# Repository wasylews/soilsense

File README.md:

# SoilSense

A low-power soil moisture and climate sensor for your garden. It samples capacitive soil moisture, temperature, and humidity, then reports them to Home Assistant. The whole device runs on an ESP-01 and is powered by a single 18650 cell, good for roughly six months per charge. It lives in a 3D-printed enclosure you can print at home.

## Features

- Battery-operated ESP-01 that deep-sleeps between readings to stretch battery life
- Single 18650 cell, estimated six months per charge
- Capacitive soil moisture probe sampled through an ADS1115 ADC
- GXHT30 digital temperature and humidity sensor
- Publishes over MQTT and the Home Assistant API, with OTA updates
- Custom two-layer PCB with a TP4056 lithium battery charger
- 3D-printed case and lid, modeled in FreeCAD and exported as STL

## Design notes

Why an ESP-01? At the time it was the smallest board I had on hand, and that was the point. I wanted to see how little hardware could still run a useful garden sensor. An ESP32 would have made this easier; it even has ADCs onboard, but easier was not the goal.

The ESP-01 has no ADC on the module, so the probe reads through an external ADS1115 on the same I2C bus as the GXHT30. The 16-bit ADC is overkill for a moisture probe, but it keeps the analog side out of the firmware and the whole board on two wires.

Deep sleep is what makes the battery life work. Between readings the chip sleeps, so the sensor sits in the soil without a cable and without frequent recharges.

## Design

### Electronics

The schematic and PCB are designed in KiCad and live in `design/soilsense/`. The board hosts an ESP-01 module, the TP4056 charger, and an I2C bus that connects the ADS1115 and the GXHT30. While the design was being refined, several board variants were explored (30x70 mm, 50x70 mm, and one rotated ESP layout); the main board is `soilsense.kicad_pcb`.

### Firmware

The firmware is an ESPHome config, `firmware/soilsense.yaml`. It reads the sensors over I2C, publishes to Home Assistant, and puts the chip to deep sleep. WiFi credentials and API keys live in a gitignored `secrets.yaml`. Flash it with:

```
esphome run soilsense.yaml
```

### Enclosure

The case is modeled in FreeCAD (`design/enclosure.FCStd`) and exported as STL for printing (`design/enclosure-case.stl` and `design/enclosure-lid.stl`). The lid snaps over the case, and the base carries a slot for the moisture probe.

## Repository layout

```
design/
  enclosure.FCStd                  FreeCAD source of the case
  enclosure-case.stl               case, ready to print
  enclosure-lid.stl                lid, ready to print
  soilsense/                       KiCad project (schematic, PCB, board variants)
firmware/
  soilsense.yaml                   ESPHome configuration
images/
  board render, PCB layout, schematic and enclosure photos
```

## Images

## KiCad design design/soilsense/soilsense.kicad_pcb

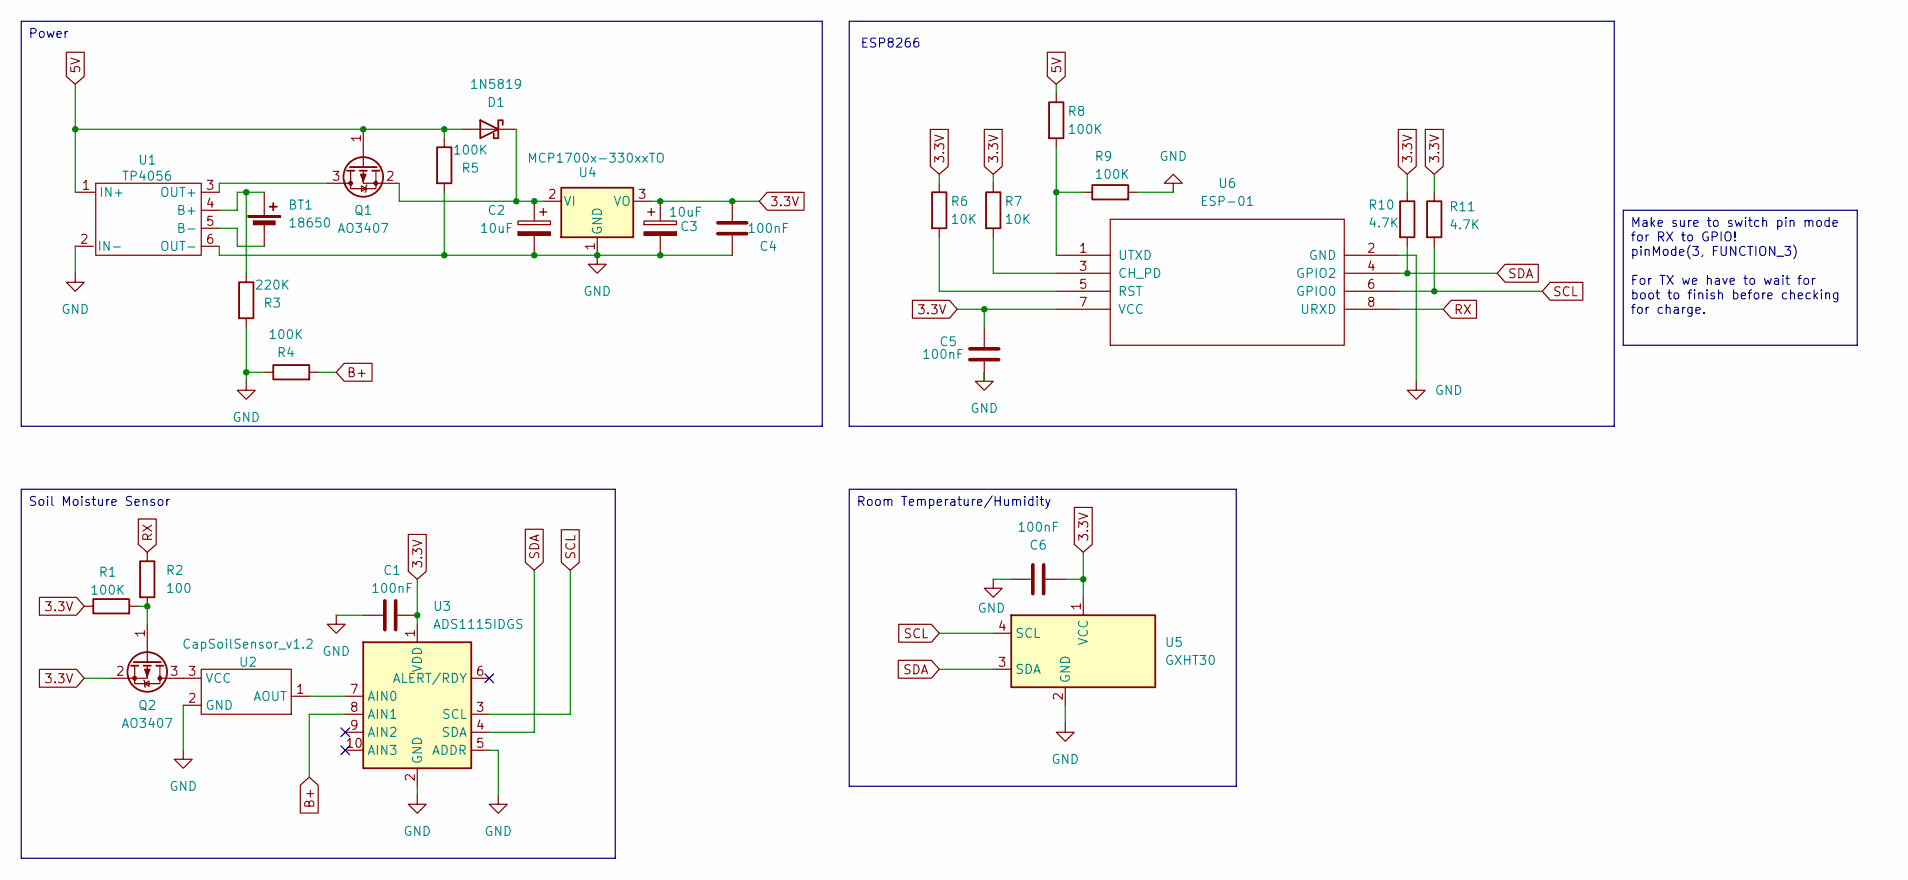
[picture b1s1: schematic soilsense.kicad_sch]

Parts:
BT1: 18650
C1, C4, C5, C6: 100nF; C_Disc_D5.0mm_W2.5mm_P5.00mm
C2, C3: 10uF; CP_Radial_D5.0mm_P2.00mm
D1: 1N5819; D_DO-41_SOD81_P10.16mm_Horizontal
Q1, Q2: AO3407; PinHeader_1x03_P2.54mm_Vertical
R1, R4, R5, R8, R9: 100K; R_Axial_DIN0204_L3.6mm_D1.6mm_P5.08mm_Horizontal
R2: 100; R_Axial_DIN0204_L3.6mm_D1.6mm_P5.08mm_Horizontal
R3: 220K; R_Axial_DIN0204_L3.6mm_D1.6mm_P5.08mm_Horizontal
R6, R7: 10K; R_Axial_DIN0204_L3.6mm_D1.6mm_P5.08mm_Horizontal
R10, R11: 4.7K; R_Axial_DIN0204_L3.6mm_D1.6mm_P5.08mm_Horizontal
U1: TP4056
U2: CapSoilSensor_v1.2; PinHeader_1x03_P2.54mm_Vertical
U3: ADS1115IDGS; PinHeader_1x10_P2.54mm_Vertical
U4: MCP1700x-330xxTO; TO-92
U5: GXHT30; PinSocket_1x04_P2.54mm_Vertical
U6: ESP-01

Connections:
3.3V: C1.2, C3.1, C4.1, C5.2, C6.2, Q2.2 (S), R1.1, R6.1, R7.1, R10.1, R11.1, U3.1 (VDD), U4.3 (VO), U5.1 (VCC), U6.7 (VCC)
5V: D1.2 (A), Q1.1 (G), R5.1, R8.1, U1.1 (IN+)
B+: R4.2, U3.8 (AIN1)
GND: C1.1, C2.2, C3.2, C4.2, C5.1, C6.1, R3.2, R4.1, R5.2, R9.2, U1.2 (IN-), U1.6 (OUT-), U2.2 (GND), U3.2 (GND), U3.5 (ADDR), U4.1 (GND), U5.2 (GND), U6.2 (GND)
unnamed: BT1.2 (-), U1.5 (B-)
unnamed: C2.1, D1.1 (K), Q1.2 (S), U4.2 (VI)
unnamed: Q1.3 (D), U1.3 (OUT+)
unnamed: Q2.3 (D), U2.3 (VCC)
unnamed: Q2.1 (G), R1.2, R2.2
unnamed: BT1.1 (+), R3.1, U1.4 (B+)
unnamed: U2.1 (AOUT), U3.7 (AIN0)
unnamed: R7.2, U6.3 (CH_PD)
unnamed: R6.2, U6.5 (RST)
unnamed: R8.2, R9.1, U6.1 (UTXD)
RX: R2.1, U6.8 (URXD)
SCL: R11.2, U3.3 (SCL), U5.4 (SCL), U6.6 (GPIO0)
SDA: R10.2, U3.4 (SDA), U5.3 (SDA), U6.4 (GPIO2)

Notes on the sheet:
ESP8266
Soil Moisture Sensor
Make sure to switch pin mode for RX to GPIO! pinMode(3, FUNCTION_3) For TX we have to wait for boot to finish before checking for charge.
Room Temperature/Humidity
Power

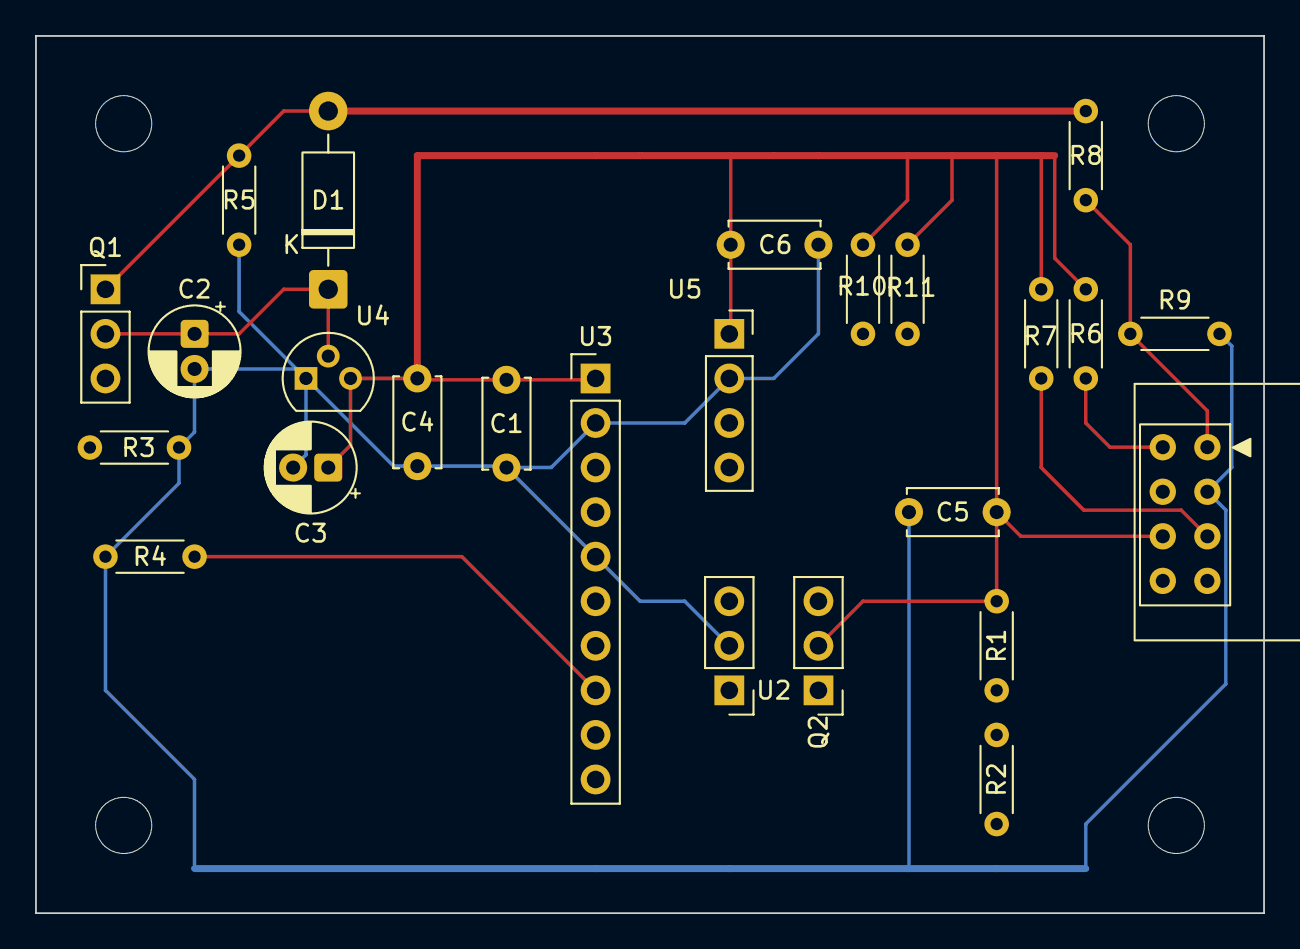
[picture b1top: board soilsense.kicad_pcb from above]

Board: 10 copper layers, 70.0 x 50.0 mm, 25 parts (0 on the bottom side), 14 nets.

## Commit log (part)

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2026-03-22 Init SoilSense
2026-05-04 Finish pcb layout
